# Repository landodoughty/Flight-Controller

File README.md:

# Flight-Controller
A Custom Flight Controller PCB I designed for one of my science fair projects.

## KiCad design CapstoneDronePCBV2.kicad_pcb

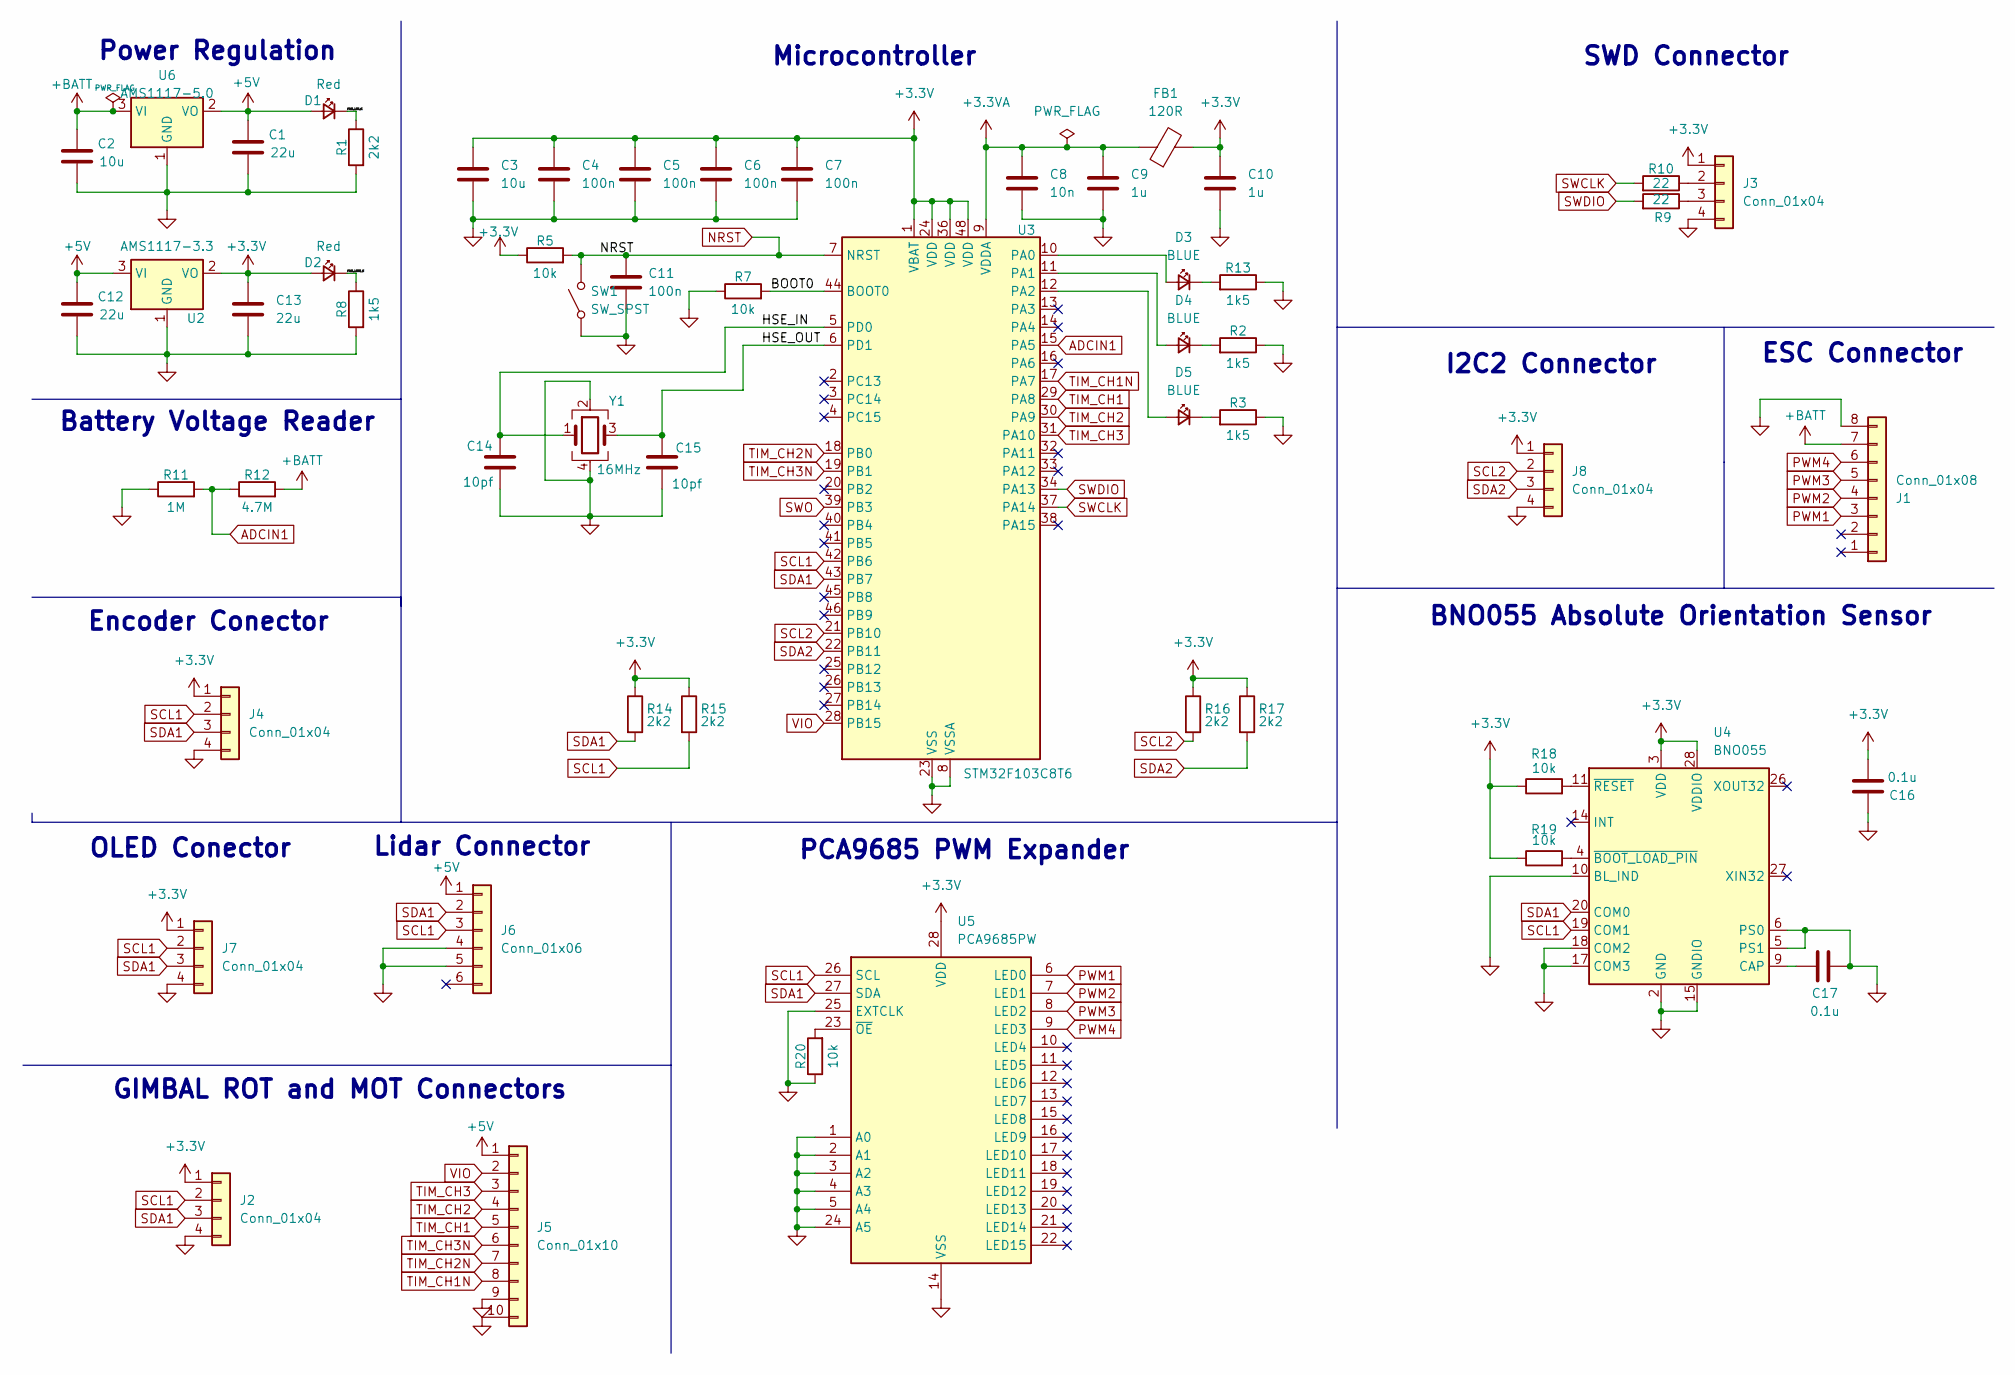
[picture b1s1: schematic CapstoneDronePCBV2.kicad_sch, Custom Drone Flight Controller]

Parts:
C1, C12, C13: 22u; C_0805_2012Metric; LCSC Part # C45783
C2: 10u; C_0805_2012Metric; LCSC Part # C1740
C3: 10u; C_0603_1608Metric; LCSC Part # C19702
C4, C5, C6, C7, C11: 100n; C_0402_1005Metric; LCSC Part # C1525
C8: 10n; C_0402_1005Metric; LCSC Part # C15195
C9, C10: 1u; C_0402_1005Metric; LCSC Part # C52923
C14, C15: 10pf; C_0402_1005Metric; LCSC Part # C32949
C16, C17: 0.1u; C_0402_1005Metric; LCSC Part # C1525
D1, D2: Red; LED_0603_1608Metric; LCSC Part # C2286
D3, D4, D5: BLUE; LED_0603_1608Metric; LCSC Part # C72038
FB1: 120R; L_0603_1608Metric
J1: Conn_01x08; JST_SH_SM08B-SRSS-TB_08x1.00mm_Angled
J2, J4, J7, J8: Conn_01x04; JST_SH_SM04B-SRSS-TB_04x1.00mm_Angled
J3: Conn_01x04; PinHeader_1x04_P2.54mm_Vertical
J5: Conn_01x10; JST_SH_SM10B-SRSS-TB_10x1.00mm_Angled
J6: Conn_01x06; JST_SH_SM06B-SRSS-TB_06x1.00mm_Angled
R1, R14, R15, R16, R17: 2k2; R_0402_1005Metric; LCSC Part # C25879
R2, R3, R8, R13: 1k5; R_0402_1005Metric; LCSC Part # C25867
R5, R7, R18, R19, R20: 10k; R_0402_1005Metric; LCSC Part # C25744
R9, R10: 22; R_0402_1005Metric; LCSC Part # C25092
R11: 1M; R_0402_1005Metric; LCSC Part # C26083
R12: 4.7M; R_0402_1005Metric
SW1: SW_SPST; SW_Push_1P1T_NO_6x6mm_H9.5mm
U2: AMS1117-3.3; SOT-223-3_TabPin2; LCSC Part # C6186
U3: STM32F103C8T6; LQFP-48_7x7mm_P0.5mm; LCSC Part # C8734
U4: BNO055; LGA-28_5.2x3.8mm_P0.5mm; LCSC Part # C93216
U5: PCA9685PW; TSSOP-28_4.4x9.7mm_P0.65mm; LCSC Part # C2678753
U6: AMS1117-5.0; SOT-223-3_TabPin2; LCSC Part # C6187
Y1: 16MHz; Crystal_SMD_3225-4Pin_3.2x2.5mm; LCSC Part # C13738

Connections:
+3.3V: C3.1, C4.1, C5.1, C6.1, C7.1, C10.1, C13.1, C16.2, D2.2 (A), FB1.2, J2.1, J3.1, J4.1, J7.1, J8.1, R5.1, R14.1, R15.1, R16.1, R17.1, R18.1, R19.1, U2.2 (VO), U3.1 (VBAT), U3.24 (VDD), U3.36 (VDD), U3.48 (VDD), U4.3 (VDD), U4.28 (VDDIO), U5.28 (VDD)
+3.3VA: C8.1, C9.1, FB1.1, U3.9 (VDDA)
+5V: C1.1, C12.1, D1.2 (A), J5.1, J6.1, U2.3 (VI), U6.2 (VO)
+BATT: C2.1, J1.7, R12.2, U6.3 (VI)
/BOOT0: R7.2, U3.44 (BOOT0)
/HSE_IN: C14.1, U3.5 (PD0), Y1.1
/HSE_OUT: C15.1, U3.6 (PD1), Y1.3
/PWR_LED2_K: D2.1 (K), R8.1
ADCIN1: R11.2, R12.1, U3.15 (PA5)
GND: C1.2, C2.2, C3.2, C4.2, C5.2, C6.2, C7.2, C8.2, C9.2, C10.2, C11.2, C12.2, C13.2, C14.2, C15.2, C16.1, C17.2, J1.8, J2.4, J3.4, J4.4, J5.9, J5.10, J6.4, J6.5, J7.4, J8.4, R1.2, R2.1, R3.1, R7.1, R8.2, R11.1, R13.1, R20.1, SW1.1 (A), U2.1 (GND), U3.8 (VSSA), U3.23 (VSS), U3.35 (VSS), U3.47 (VSS), U4.2 (GND), U4.5 (PS1), U4.6 (PS0), U4.10 (BL_IND), U4.15 (GNDIO), U4.16 (GNDIO), U4.17 (COM3), U4.18 (COM2), U4.25 (GNDIO), U5.1 (A0), U5.2 (A1), U5.3 (A2), U5.4 (A3), U5.5 (A4), U5.14 (VSS), U5.24 (A5), U5.25 (EXTCLK), U6.1 (GND), Y1.2, Y1.4
NRST: C11.1, R5.2, SW1.2 (B), U3.7 (NRST)
unnamed: D1.1 (K), R1.1
unnamed: D3.2 (A), U3.10 (PA0)
unnamed: D3.1 (K), R13.2
unnamed: D4.2 (A), U3.11 (PA1)
unnamed: D4.1 (K), R2.2
unnamed: D5.2 (A), U3.12 (PA2)
unnamed: D5.1 (K), R3.2
unnamed: J3.2, R10.1
unnamed: J3.3, R9.1
unnamed: C17.1, U4.9 (CAP)
unnamed: R19.2, U4.4 (~BOOT_LOAD_PIN)
unnamed: R18.2, U4.11 (~RESET)
unnamed: R20.2, U5.23 (~OE)
PWM1: J1.3, U5.6 (LED0)
PWM2: J1.4, U5.7 (LED1)
PWM3: J1.5, U5.8 (LED2)
PWM4: J1.6, U5.9 (LED3)
SCL1: J2.2, J4.2, J6.3, J7.2, R15.2, U3.42 (PB6), U4.19 (COM1), U5.26 (SCL)
SCL2: J8.2, R16.2, U3.21 (PB10)
SDA1: J2.3, J4.3, J6.2, J7.3, R14.2, U3.43 (PB7), U4.20 (COM0), U5.27 (SDA)
SDA2: J8.3, R17.2, U3.22 (PB11)
SWCLK: R10.2, U3.37 (PA14)
SWDIO: R9.2, U3.34 (PA13)
SWO: U3.39 (PB3)
TIM_CH1: J5.5, U3.29 (PA8)
TIM_CH1N: J5.8, U3.17 (PA7)
TIM_CH2: J5.4, U3.30 (PA9)
TIM_CH2N: J5.7, U3.18 (PB0)
TIM_CH3: J5.3, U3.31 (PA10)
TIM_CH3N: J5.6, U3.19 (PB1)
VIO: J5.2, U3.28 (PB15)

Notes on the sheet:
Lidar Connector
OLED Conector
BNO055 Absolute Orientation Sensor
Encoder Conector
GIMBAL ROT and MOT Connectors
Battery Voltage Reader
Power Regulation
Microcontroller
I2C2 Connector
PCA9685 PWM Expander
ESC Connector
SWD Connector

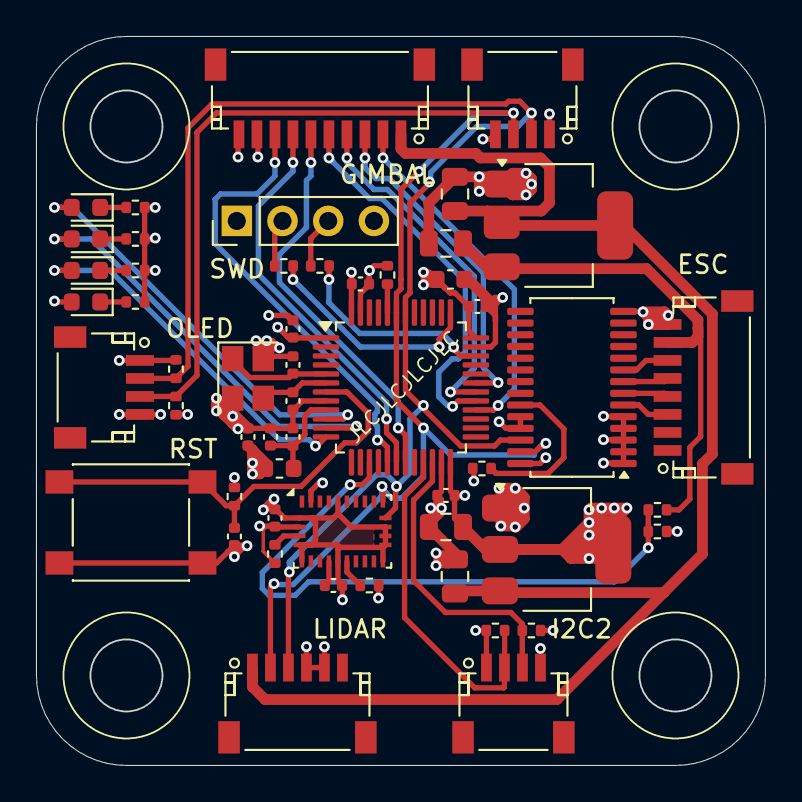
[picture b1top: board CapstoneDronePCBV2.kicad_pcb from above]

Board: 4 copper layers, 40.5 x 40.5 mm, 53 parts (0 on the bottom side), 40 nets.

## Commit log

2025-07-30 PCB files
